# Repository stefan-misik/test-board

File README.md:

# test-board
Simple development board with interface to Nokia 5110 display and matrix keypad and two outputs based on Atmega328 microcontroller

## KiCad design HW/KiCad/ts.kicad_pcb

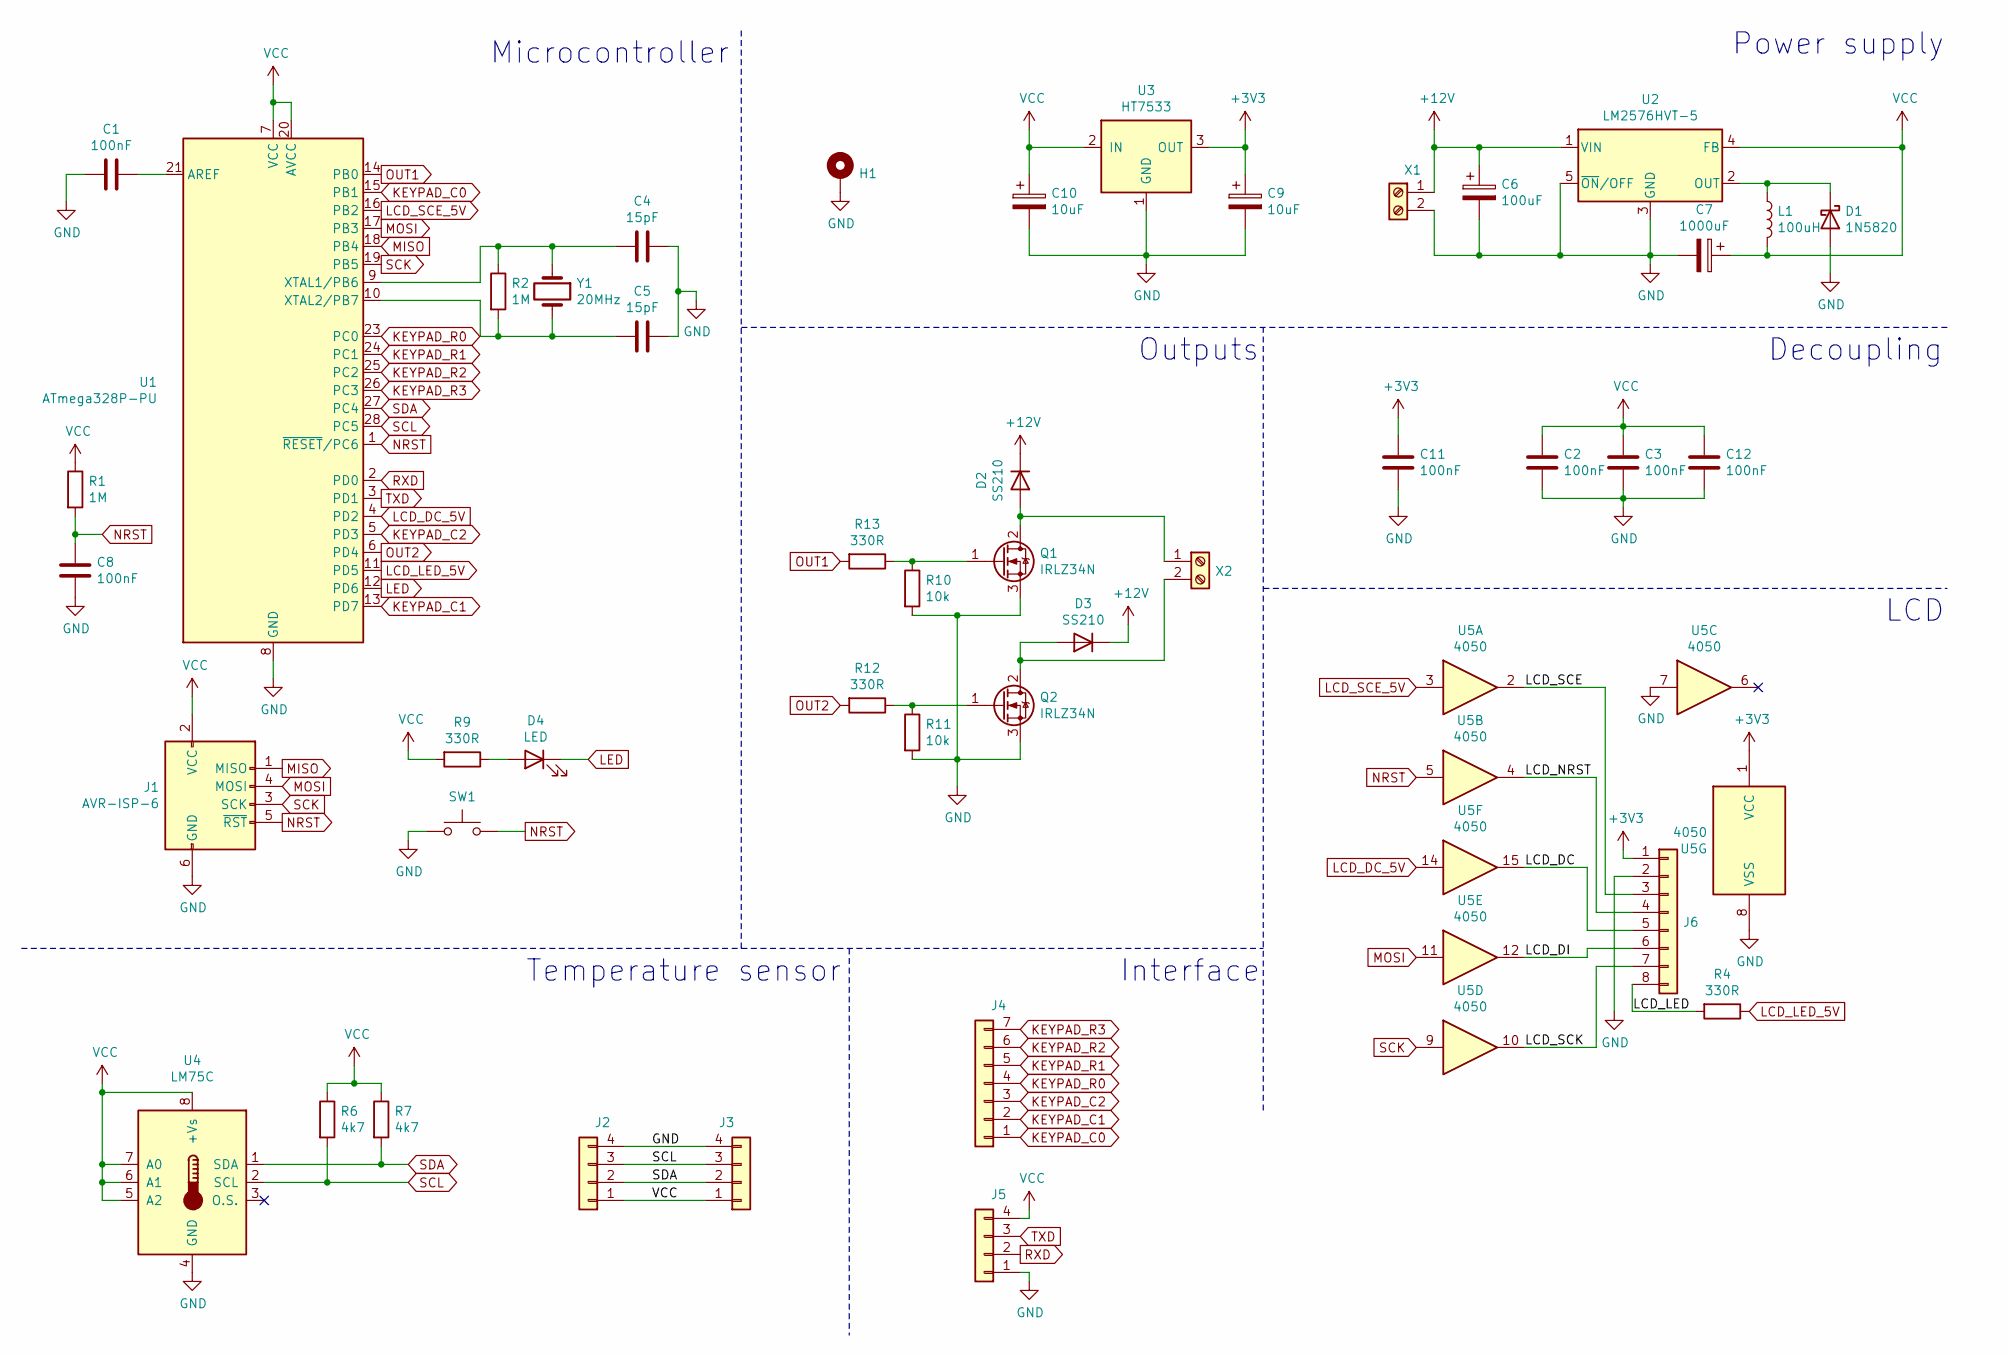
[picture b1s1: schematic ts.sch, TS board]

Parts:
C1, C2, C3, C8, C11, C12: 100nF; C_0805_2012Metric
C4, C5: 15pF; C_0805_2012Metric
C6: 100uF; CP_Radial_D8.0mm_P3.80mm
C7: 1000uF; CP_Radial_D10.0mm_P5.00mm
C9, C10: 10uF; CP_Elec_5x5.4
D1: 1N5820; D_DO-201AD_P15.24mm_Horizontal
D2, D3: SS210; D_SMB
D4: LED; LED_D5.0mm
H1: MountingHole_Pad; MountingHole_3.5mm_Pad
J1: AVR-ISP-6; PinHeader_2x03_P2.54mm_Vertical
J2, J3, J5: Conn_01x04; PinHeader_1x04_P2.54mm_Vertical
J4: Conn_01x07; PinHeader_1x07_P2.54mm_Vertical
J6: Conn_01x08; PinHeader_1x08_P2.54mm_Vertical
L1: 100uH; L_Toroid_Vertical_L16.4mm_W7.6mm_P6.60mm_Vishay_TJ3
Q1, Q2: IRLZ34N; TO-220-3_Vertical
R1, R2: 1M; R_0805_2012Metric
R4, R9, R12, R13: 330R; R_0805_2012Metric
R6, R7: 4k7; R_0805_2012Metric
R10, R11: 10k; R_0805_2012Metric
SW1: RESET; SW_PUSH_6mm
U1: ATmega328P-PU; DIP-28_W7.62mm_Socket
U2: LM2576HVT-5; TO-220-5_Vertical
U3: HT7533; TO-92
U4: LM75C; SOIC-8_3.9x4.9mm_P1.27mm
U5: 4050; SOIC-16_3.9x9.9mm_P1.27mm
X1, X2: Screw_Terminal_01x02; TerminalBlock_bornier-2_P5.08mm
Y1: 20MHz; Crystal_HC49-4H_Vertical

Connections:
+3V3: C9.1, C11.1, J6.1, U3.3 (OUT), U5.1 (VCC)
+12V: C6.1, D2.1 (K), D3.1 (K), U2.1 (VIN), X1.1
/LCD_DC: J6.5, U5.15
/LCD_DI: J6.6, U5.12
/LCD_LED: J6.8, R4.2
/LCD_NRST: J6.4, U5.4
/LCD_SCE: J6.3, U5.2
/LCD_SCK: J6.7, U5.10
GND: C1.2, C2.2, C3.2, C4.1, C5.1, C6.2, C7.2, C8.1, C9.2, C10.2, C11.2, C12.2, D1.2 (A), H1.1, J1.6 (GND), J2.4, J3.4, J5.1, J6.2, Q1.3 (S), Q2.3 (S), R10.2, R11.2, SW1.1, U1.8 (GND), U1.22 (GND), U2.3 (GND), U2.5 (~ON~/OFF), U3.1 (GND), U4.4 (GND), U5.7, U5.8 (VSS), X1.2
KEYPAD_C0: J4.1, U1.15 (PB1)
KEYPAD_C1: J4.2, U1.13 (PD7)
KEYPAD_C2: J4.3, U1.5 (PD3)
KEYPAD_R0: J4.4, U1.23 (PC0)
KEYPAD_R1: J4.5, U1.24 (PC1)
KEYPAD_R2: J4.6, U1.25 (PC2)
KEYPAD_R3: J4.7, U1.26 (PC3)
LCD_DC_5V: U1.4 (PD2), U5.14
LCD_LED_5V: R4.1, U1.11 (PD5)
LCD_SCE_5V: U1.16 (PB2), U5.3
LED: D4.1 (K), U1.12 (PD6)
MISO: J1.1 (MISO), U1.18 (PB4)
MOSI: J1.4 (MOSI), U1.17 (PB3), U5.11
NRST: C8.2, J1.5 (~RST), R1.2, SW1.2, U1.1 (~RESET~/PC6), U5.5
unnamed: C1.1, U1.21 (AREF)
unnamed: C4.2, R2.1, U1.9 (XTAL1/PB6), Y1.1
unnamed: C5.2, R2.2, U1.10 (XTAL2/PB7), Y1.2
unnamed: D1.1 (K), L1.1, U2.2 (OUT)
unnamed: D2.2 (A), Q1.2 (D), X2.1
unnamed: D3.2 (A), Q2.2 (D), X2.2
unnamed: D4.2 (A), R9.1
unnamed: Q1.1 (G), R10.1, R13.1
unnamed: Q2.1 (G), R11.1, R12.1
OUT1: R13.2, U1.14 (PB0)
OUT2: R12.2, U1.6 (PD4)
RXD: J5.2, U1.2 (PD0)
SCK: J1.3 (SCK), U1.19 (PB5), U5.9
SCL: J2.3, J3.3, R6.2, U1.28 (PC5), U4.2 (SCL)
SDA: J2.2, J3.2, R7.2, U1.27 (PC4), U4.1 (SDA)
TXD: J5.3, U1.3 (PD1)
VCC: C2.1, C3.1, C7.1, C10.1, C12.1, J1.2 (VCC), J2.1, J3.1, J5.4, L1.2, R1.1, R6.1, R7.1, R9.2, U1.7 (VCC), U1.20 (AVCC), U2.4 (FB), U3.2 (IN), U4.5 (A2), U4.6 (A1), U4.7 (A0), U4.8 (+Vs)

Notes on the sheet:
Temperature sensor
Interface
Microcontroller
Power supply
Decoupling
LCD
Outputs

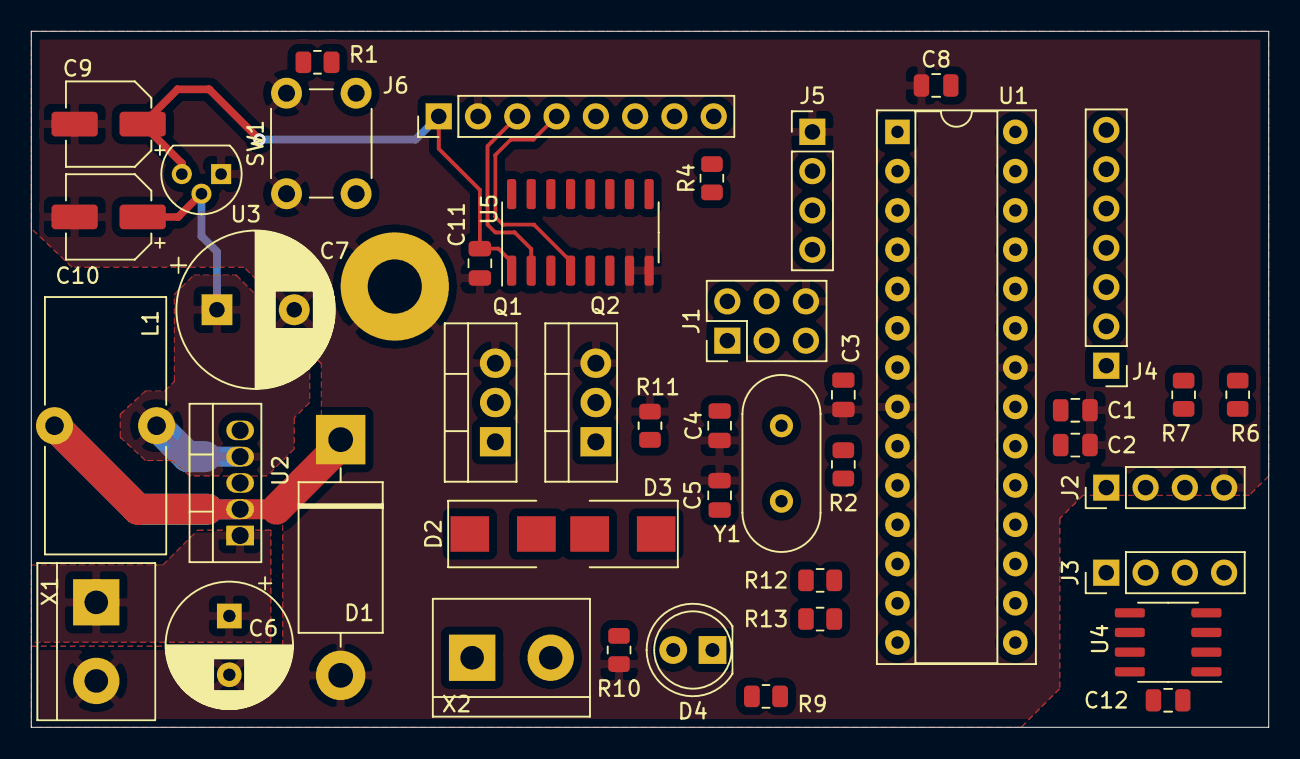
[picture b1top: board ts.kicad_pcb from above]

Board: 2 copper layers, 80.0 x 45.0 mm, 45 parts (0 on the bottom side), 40 nets.

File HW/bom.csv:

Qty;Value;Device;Package;Parts;Description;gme.cz;Price (CZK)
1;;10-XX;B3F-10XX;RESET;OMRON SWITCH;630-305;3,3
1;;DIODE-MINIMELF;MINIMELF;D4;DIODE;917-054;0,88
1;;LED5MM;LED5MM;LED1;LED;"511-226; 511-227";2,2
1;;MA03-1;MA03-1;UART;PIN HEADER;832-021;11
1;;MA03-2;MA03-2;ICSP;PIN HEADER;832-035;9,6
1;;MA07-1;MA07-1;KEYPAD;PIN HEADER;832-021;
1;;MA08-1;MA08-1;LCD;PIN HEADER;832-021;
2;;W237-102;W237-102;X1, X2;WAGO SCREW CLAMP;821-134;3,2
2;0R;R-EU_R0805;R0805;R3, R5;RESISTOR, European symbol;901-170;1,1
1;1000uF;CPOL-EUTT5D10;TT5D10;C7;POLARIZED CAPACITOR, European symbol;123-776;4,4
6;100nF;C-EUC0805;C0805;C1, C2, C3, C8, C11, C12;CAPACITOR, European symbol;906-096;0,75
1;100uF;CPOL-EUTAP5-80;TAP5-80;C6;POLARIZED CAPACITOR, European symbol;123-451;0,61
1;100uH;L-USTJ3-U1;TJ3-U1;L1;INDUCTOR, American symbol;611-140;19
3;10k;R-EU_R0805;R0805;R1, R10, R11;RESISTOR, European symbol;901-003;0,85
2;10uF;CPOL-EUC;PANASONIC_C;C9, C10;POLARIZED CAPACITOR, European symbol;908-003;2,6
2;15pF;C-EUC0805;C0805;C4, C5;CAPACITOR, European symbol;906-078;0,96
1;1M;R-EU_R0805;R0805;R2;RESISTOR, European symbol;901-182;1,2
1;1N582X;1N582X;DIODE5MM;D1;;223-004;3,1
1;20 MHz;CRYSTALHC49S;HC49/S;Q1;CRYSTAL;131-027;11
4;330R;R-EU_R0805;R0805;R4, R9, R12, R13;RESISTOR, European symbol;901-083;0,85
3;4.7k;R-EU_R0805;R0805;R6, R7, R8;RESISTOR, European symbol;901-115;0,85
1;4050D;4050D;SO16;IC1;Hex non-inverting BUFFER;953-067;6,6
1;ATMEGA328P-PU;ATMEGA328P-PU;DIP254P762X457-28;U1;8-bit Microcontroller with In-System Programmable Flash;432-228;94
1;HT7533;LE33CZ;TO-92;U3;;330-117;24
2;IRFZ24N;IRFZ24N;TO220AB;T1, T2;;213-208;12
1;LM2576T;LM2576T;TO220-5;U2;;330-113;40
1;LM75;LM75;SOIC8;U4;;969-012;18
1;MOUNT-PAD-ROUND3.6;MOUNT-PAD-ROUND3.6;3,6-PAD;H1;MOUNTING PAD, round;;
2;SS210;DIODE-SMB;SMB;D2, D3;DIODE;920-123;2,6

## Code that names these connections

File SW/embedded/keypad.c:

#include "keypad.h"
#include "common.h"
#include <avr/pgmspace.h>


#define keypad_get_rows() (PINC & 0x0f)

/**
 * @brief Keypad layout
 * 
 */
static const unsigned char keypad_layout[4][3] PROGMEM =
{
    {'1', '2', '3'},
    {'4', '5', '6'},
    {'7', '8', '9'},
    {'*', '0', '#'}
};


static char keypad_get_column(
    char column 
)
{
    unsigned char rows = keypad_get_rows();
    char pos;
    
    for(pos = 0; pos < 4; pos ++)
    {
        if(0 == (0x08 & rows))
            return pgm_read_byte(&(keypad_layout[pos][column]));
        
        rows <<= 1;
    }

    return '\0';
}

/******************************************************************************/
void keypad_init(
    void
)
{
    /* port connection: columns: PB1, PB2, PD7 and rows: PC0 - PC3 */
    
    /* Make sure internal pull-ups are not disabled */
    MCUCR &= ~(1 << PUD);
    
    /* Set all keypad pins as inputs to enable pull-ups */
    DDRB &= ~((1 << DDB1));
    DDRD &= ~((1 << DDD3) | (1 << DDD7));
    DDRC &= ~((1 << DDC0) | (1 << DDC1) | (1 << DDC2) | (1 << DDC3));
    
    /* Turn on the internal pull-ups */
    PORTB |= ((1 << PORTB1));
    PORTD |= ((1 << PORTD3) | (1 << PORTD7));
    PORTC |= ((1 << PORTC0) | (1 << PORTC1) | (1 << PORTC2) | (1 << PORTC3));
}

/******************************************************************************/
char keypad_get(
    void
)
{
    char key = '\0';

    /* Select first column */
    PORTD &= ~(1 << PORTD3);
    DDRD |= (1 << DDD3);
    /* Read key */
    key = keypad_get_column(0);
    /* De-select first column */
    DDRD &= ~(1 << DDD3);
    PORTD |= (1 << PORTD3);

	if ('\0' != key)
	{
		return key;
	}
    
    /* Select second column */
    PORTB &= ~(1 << PORTB1);
    DDRB |= (1 << DDB1);
    /* Read key */
    key = keypad_get_column(2);
    /* De-select second column */
    DDRB &= ~(1 << DDB1);
    PORTB |= (1 << PORTB1);

	if ('\0' != key)
	{
		return key;
	}
    
    /* Select first column */
    PORTD &= ~(1 << PORTD7);
    DDRD |= (1 << DDD7);
    /* Read key */
    key = keypad_get_column(1);
    /* De-select first column */
    DDRD &= ~(1 << DDD7);
    PORTD |= (1 << PORTD7);
    
    return key;
}

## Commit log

2015-01-07 Created directory structure
2015-01-07 Eagle description files, Design rules for iteadstudio
2015-01-07 Designed power supply
2015-01-07 Deleted files
2015-01-07 Ignored files
2015-01-08 3.3v supply
2015-01-08 v-regulators library
2015-01-08 Added level shifter CMOS 4050
2015-01-08 Added Eagle Libraries
2015-01-08 Many changes
2015-01-08 Moved power pins of 4050
2015-01-08 Resized analog ground
2015-01-08 Commit before changing to digital temperature sensor
2015-01-09 Big Update
2015-01-09 Swaped LCD_SCE_5V and LCD_DC_5V signals on 4050
2015-01-09 Added Power CMOS transistors
2015-01-10 HW Release 1
2015-01-10 Minor HW changes
2015-01-10 Timer 1 is no longer used for PWM
2015-01-10 Minor HW Updates
2015-01-10 Preparing Gerber files
2015-01-10 Generated final version of gerber files
2015-01-12 Added graphTest tool
2015-01-12 Removed unnecessary file
2015-01-13 Ignored some files
2015-01-15 Added filters into visual studio project
2015-01-19 Ignored Eagle backup files
2015-01-19 Added value of crystal
2015-01-19 Created BOM file
2015-01-19 Added order numbers in bom.csv
2015-01-22 Ignored pdb files
2015-01-22 Modified drawing technique
2015-01-22 Added Graphical library
2015-01-26 Added PCB images
2015-01-26 Modified PCB images
2015-02-01 Changed diameters of vias
2015-02-01 Changed faulty size of via
2015-03-31 Added lcd driver files
2015-03-31 minor update
2015-03-31 Added SPI communication
2015-04-01 Added module for controling outputs
2015-04-01 Working initialization, lcd parameters configuration and simple drawing
2015-04-02 Added text drawing functionality
2015-04-02 Added comments
2015-04-02 Added Main fiele, makefile and atmel studio solution to embedded part of the software
2015-04-02 Added temperature sensor driver
2015-04-02 Simple temperature meter
2015-04-03 LCD backlight and LED controlled by PWM
2015-04-03 Added function to read graphic data from display buffer
2015-04-03 Replaced inefective modulus operations
2015-04-03 Temperature resolution changed to quarter of dg
2015-04-08 Added timer module
2015-04-10 Replaced R1 due to improper LCD reset procedure
2015-04-12 Added size statistics after build
2015-04-12 Lcd content update by providing rectangle to update
2015-04-17 Temperature is read using interrupts
2015-04-18 Temperature measurement made more fail-proof
2015-04-18 Added new-lines at the end of c files
2015-04-20 Removed unnecessary typedef
2015-04-20 Comments added
2015-04-20 Added function to check status of temperature measurement
2015-04-21 Tabs replaced with spaces
2015-04-21 Added some alarm functionality to timer module
2015-04-22 Alarm functionality moved into separate module
2017-12-09 [SW] Minor changes in LCD, added keypad
    Added correct stdio putchar function for LCD. Added keypad source files.
2017-12-12 [HW] Updated PCB
    Fixed keypad connection. Removed copper from underneath the temperature
    sensor. Made temperature sensor removable.
2017-12-13 [SW] Fixed LCD redraw
2017-12-13 [HW] LCD chip select
    Using NSS microcontroller output to drive LCD chip select.
2017-12-15 [SW] Minor changes, added more LCD characters
2017-12-15 [SW] Fixed SPI clock speed for LCD
2017-12-15 [SW] Updated keypad driver
2017-12-20 [HW] Minor modifications
2017-12-21 [HW] Removed some parts, updated layout
    Removed unessential parts (0 Ohm resistor, reset pin protection diode).
    Optimized layout to optimize some connections.
2018-01-02 [HW] Minor change
2018-04-14 [HW] Organized schematics
2018-11-20 [HW] Resolved some design DRC and ERC warnings
2018-11-25 [HW] Removed old gerber files
2018-12-15 [HW] Added KiCad project with schematics
2018-12-16 [HW] Fixed issues in the KiCad schematics
    Fixed some footprints associations, 4050 buffer power supply.
2018-12-17 [SW] Modifications for the 2nd revision of the HW
2018-12-18 [SW] Basic keypad driver
2019-02-04 [SW] Added FIFO tests
2019-02-04 [SW] Ignored VS code project settings
2019-02-05 [SW] Added FIFO tests and functionality
2020-11-11 [SW] Add fuses programming
2020-12-18 [HW] Place KiCad layout components
2020-12-20 [HW] Add some layout
